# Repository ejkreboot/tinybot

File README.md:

tinybot
=======

Rechargeable, customizable robots inspired by https://hackaday.io/project/581-Tiny-robot-family

NOTE: This initial design is completely untested.  Please verify schematic and board prior to manufacturing boards.

The idea here is to create a education platform for embedded computing and basic robotics.  

A drawback of this design is the use of a few surface mount components.  This is to avoid use of through hole packages for MOSFETs which are relatively large.

This design incorporates a charging circuit.  Plugging in the robot to a USB charger will charge a lithium ion cell inserted into the batter holder.  This circuit is designed to charge at 100mA.

To use the robot, pager vibrator type motors must be soldered to the motor pads (one on the left, one on the right) and then hot glued in place (see https://hackaday.io/project/581-Tiny-robot-family).  The ATtiny must be programmed prior to inserting into the socket (again, see https://hackaday.io/project/581-Tiny-robot-family).

The PCB includes a prototyping area with adjacent power rails to allow adding sensors/actuators to the free pins of the ATtiny.

The ATtiny can NOT be programmed in place with this design (that would require additional circuitry to isolate the ATtiny during programming).  However, the ATtiny can be programmed on a breadboard by an Arduino running the ArduinoISP sketch (see http://www.instructables.com/id/Program-an-ATtiny-with-Arduino/).  

Please lend a hand and correct/improve the design!

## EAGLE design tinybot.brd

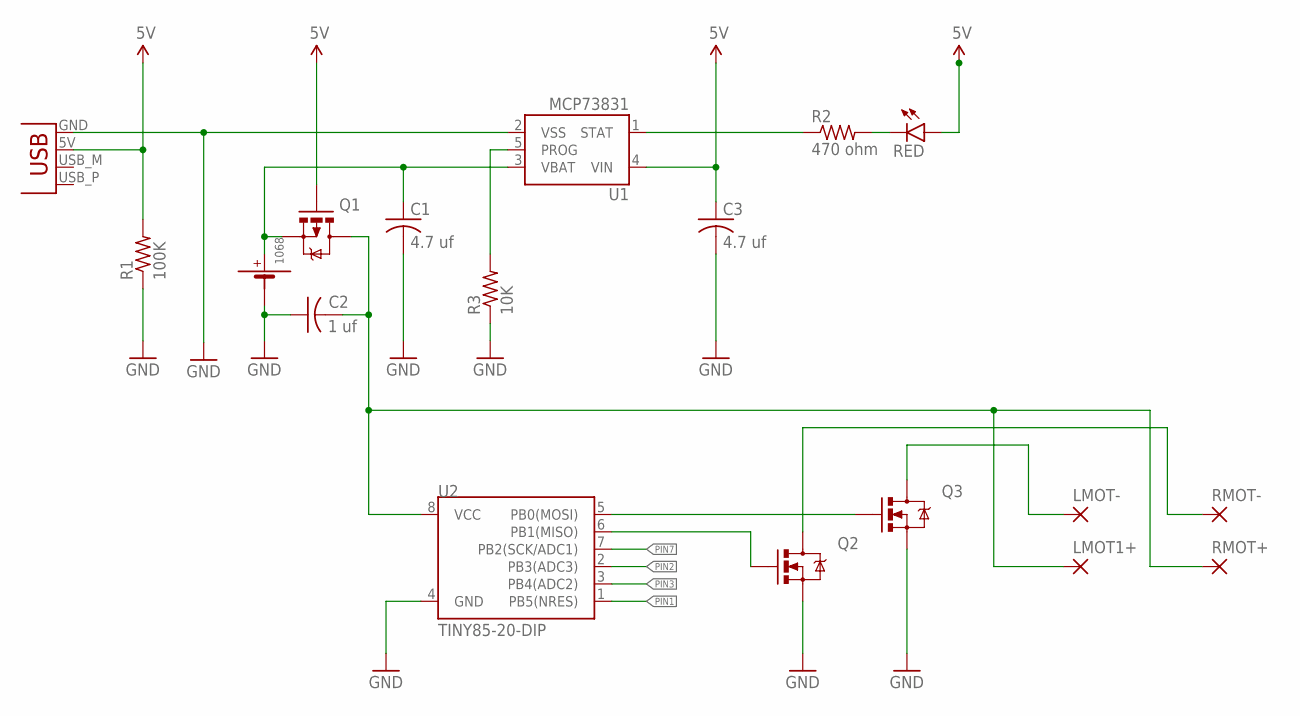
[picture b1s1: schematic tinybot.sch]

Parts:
C1, C3: 4.7 uf; C025-025X050
C2: 1 uf; C025-025X050
JP1: USBPCB; USB-A-PCB
LMOT1+: WIREPADSMD1,27-254; SMD1,27-2,54
LMOT-: WIREPADSMD1,27-254; SMD1,27-2,54
Q1: MOSFET-PCHANNEL; SOT23-3
Q2, Q3: 2N7002PW; SOT23
R1: 100K; 0204/5
R2: 470 ohm; 0204/5
R3: 10K; 0204/5
RED: LED3MM
RMOT+: WIREPADSMD1,27-254; SMD1,27-2,54
RMOT-: WIREPADSMD1,27-254; SMD1,27-2,54
U1: MCP73831; SOT23-5
U2: TINY85-20-DIP; DIP08
U$1: 1068; KEYSTONE1068

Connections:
5V: C3.1, JP1.5V (VBUS), Q1.1 (G), R1.2, RED.A, U1.4 (VIN)
GND: C1.2, C2.1, C3.2, JP1.GND, Q2.2 (S), Q3.2 (S), R1.1, R3.1, U1.2 (VSS), U2.4 (GND), U$1.NEG (-)
unnamed: R2.2, RED.K (C)
unnamed: R2.1, U1.1 (STAT)
unnamed: Q3.1 (G), U2.5 (PB0(MOSI))
unnamed: Q2.1 (G), U2.6 (PB1(MISO))
unnamed: LMOT-.1, Q3.3 (D)
unnamed: Q2.3 (D), RMOT-.1
unnamed: R3.2, U1.5 (PROG)
PIN1: U2.1 (PB5(NRES))
PIN2: U2.2 (PB3(ADC3))
PIN3: U2.3 (PB4(ADC2))
PIN7: U2.7 (PB2(SCK/ADC1))
VBAT: C1.1, Q1.2 (S), U1.3 (VBAT), U$1.POS (+)
VCC: C2.2, LMOT1+.1, Q1.3 (D), RMOT+.1, U2.8 (VCC)

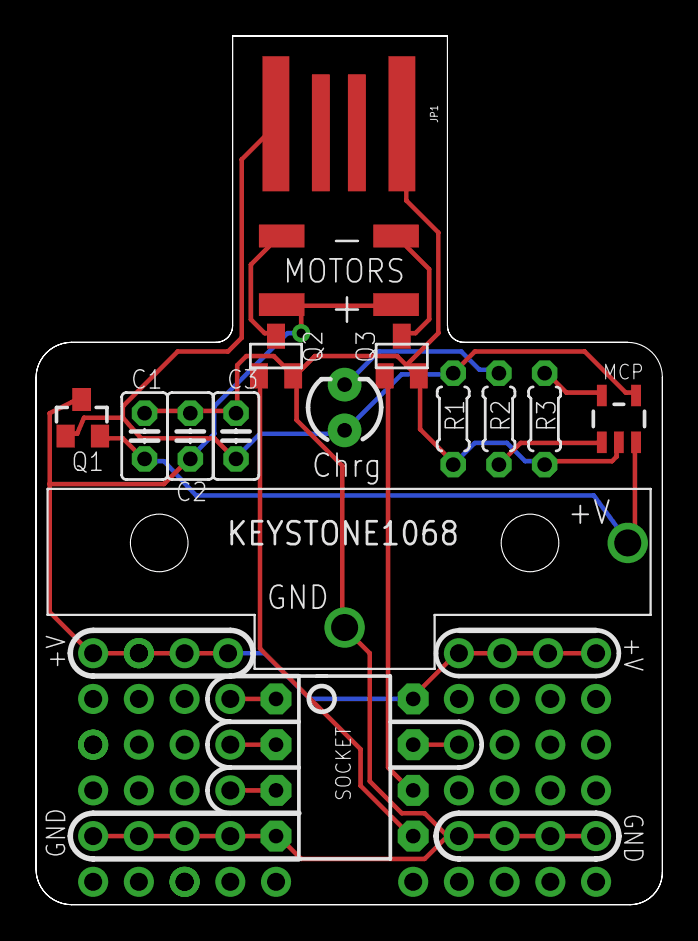
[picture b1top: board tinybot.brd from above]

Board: 2 copper layers, 34.8 x 48.3 mm, 18 parts (0 on the bottom side), 11 nets.

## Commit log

2014-07-23 Added board, schematic, and library files
2014-07-23 Updated board labels, added BOM
2014-07-24 update milling layer with board outline
2014-07-24 fixed mosfet wiring error
2014-07-25 fixed motor mosfet wiring (again)
    Still had it wrong! Motor mosfets connected to 5V (from USB), not VCC.
    Now fixed.
    Also added logo/name/url to bottom silk!
2014-07-25 Updated BOM (tinybot.csv)
2014-07-26 Updated BOM
    Update BOM, now in both excel and csv formats
2014-07-28 updated BOM
2014-07-28 Decreased charge current from 500mA to 100mA
    R3 changed from 2K to 10K
2014-07-28 Update README to reflect lower charge current
2014-12-01 improved mosfet pad layout and corrected battery holder hole size

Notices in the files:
parts and their libraries:
SparkFun-LED: Licensing: Creative Commons ShareAlike 4.0 International - https://creativecommons.org/licenses/by-sa/4.0
